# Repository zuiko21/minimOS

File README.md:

*This project is under [the MIT License](https://opensource.org/licenses/MIT), see LICENSE for details.*

# minimOS

*Please note that this doc is OBSOLETE. Read about [updated details in the new 
architecture.md](architecture.md) file.*

#### Minimalistic, portable, scalable Operating System for everything from embedded devices to (quasi) full-featured desktop computers!

## Purpose
Currently in a VERY early development stage, hopefully will become a common reference platform for deployment of computer-related appliances -- think about embedded systems, like the original intent: an Actual Exposure Time Meter for classic photographic cameras. But by virtue of its modularity and scalability would equally serve to a whole breed of home-made, retro-inspided computers.

## Future ports
Initial target is the venerable 65(C)02 and its big brother, the 16-bit enabled 65816 (port known as minimos·16) which will keep compatibility with existing '02 code. But other ports to many CPU architectures are in mind, like the Motorola 68xx / Hitachi 63xx series (minimOS·63, with the interesting 6809/6309 branch as minimOS·69), 680x0 (minimOS·68), 8080/8085/Z80 (minimOS·80), even (God forbid! :-) the commonly used x86 (minimOS·86). I really have little-to-no knowledge about this CPU family, nor about the usual IBM-based PC architecture; hopefully someone will be able to port minimOS without too much of a chore, that would give a very interesting 'breath' to (otherwise useless) older PCs.

## Supported architectures
This section has been moved to the [hardware section](hard/README.md)

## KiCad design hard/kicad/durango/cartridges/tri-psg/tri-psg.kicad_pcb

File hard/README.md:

# Hardware for minimOS

## Supported architectures

With great embarrassment I have to admit never having owned a 65xx computer...
but suport for these classic machines shouldn't be difficult to add -- for
instance, I have declared as 'reserved' the two first zero-page bytes in case
the utterly popular Commodore-64 (using a 6510) is targeted.

Back to my **own-designed** devices, here's the range (past, present and future):

## (Simple) Computers

### 65x02-based

[**MTE** _("Medidor de Tiempos de Exposición", Exposure Time Meter)_](computers/mte.md)

  * Status: finishing design.
  * Form-factor: soldered PCB.
  * Specs: 1 MHz **6503** (28 pin, 4 kiB addressing space), **128-byte RAM**,
3 kiB-EPROM (useable range from a 2732), VIA 6522
  * Peripherals: four (very large) **7-segment LED digits**, light sensor,
a couple of buttons...

[**SDd** _("Sistema de Desarrollo didáctico", Learning Development System)_](computers/sdd.md)

  * Status: [WORKING!](https://twitter.com/zuiko21/status/936654607014653952?s=19)
  * Form-factor: [solderless breadboard.](https://flic.kr/s/aHsjCMszTY)
  * Specs: 1 MHz 65SC02 (only 13 address bits used), **2 kiB RAM, 2-4 kIB (E)EPROM**,
VIA 65C22.
  * Peripherals: Amplified piezo buzzer between PB7-CB2,
currently with a VIA-attached 4-digit **LED-keypad**.

[**CHIHUAHUA**](computers/chihuahua.md)

  * Status: Finished and _sort-of_ working, but with some strange bug around VIA access,
not solved yet. _Likely to be discarded_.
  * Form-factor: [Perfboard with point-to-point soldering.](https://flic.kr/s/aHsjEn5ntM)
  * Peripherals: Piezo buzzer between PB7-CB2
  * Interfaces: **SS-22** and _old **VIAport**_ connectors.

> Soldered, compact version of [SDd](sdd.md).

[**CHIHUAHA PLUS**](computers/chihuahuaplus.md)

  * Status: [under construction (recently redesigned).](https://flic.kr/s/aHsjEGuCH3)
  * Form-factor: Perfboard with point-to-point soldering.
  * Specs: **1 MHz (socketed XTAL)** 65C02, **16 kiB RAM, 32 kiB EPROM**, VIA 65C22.
_Can be configured for **32 kiB RAM + 16 kiB EPROM** if desired_.
  * Peripherals: _Amplified_ piezo buzzer between PB7-CB2
  * Interfaces: **SS-22** and _old **VIAport**_ connectors.

[**miniKIM**](computers/minikim.md)

  * Status: finishing specs.
  * Form-factor: Perfboard with point-to-point soldering.
  * Specs: 1 MHz 6502, **32 kiB RAM (16 KiB available), 2x16 kiB EPROM**, 2xVIA 6522,
ready for _cheap video_ output. _May use 32K RAM and 16K EPROM_ instead.
  * Peripherals: original KIM keypad, **6x seven-segment displays** (muxed LTC4622).
  * Interfaces: original Application & Expansion slots, _upstream tap_ for **cheap video**.

[**DURANGO**](computers/durango.md)

  * Status: **working**.
  * Form-factor: several solderless breadboards.
  * Specs: 1 MHz 6502, **32 kiB RAM, 16 kiB EPROM**, includes **picoVDU**
TV video output (128x128 _bitmap_).
  * Peripherals: simple bit buzzer, **2x seven-segment displays** (muxed LTC4622).
  * Interfaces: 8-bit input (`IO9`), 8-bit output for _picoVDU_ (`IO8`)

> Originally intended as a **6502 CPU tester** with _no I/O_ whatsoever, it evolved
into a fully featured development platform with sort-of integrated **video output**.
_May become a definitive, improved version in perfboard_

[**miniPET**](computers/minipet.md)

  * Status: **essentially finished** design.
  * Form-factor: Perfboard with point-to-point soldering.
  * Specs: **1.57 MHz** 65(C)02, **32 kiB SRAM** (plus 2 kiB _VRAM_), up to
**32 kiB EPROM**, VIA 65(C)22, PIA 6521/6821, CRTC HD6845, with _optional second PIA_
for **IEEE-488** interface.
  * Interfaces: **same as the original PET**; cassette and IEEE-488 on separate
_optional_ board.

> _This is a recreation of the **Commodore PET/CBM 8032**, 
switchable between **40 and 80 columns**_, with updated components
(e.g. SRAM) and **VGA-compatible** output (thus about **57% faster**).

[**Tampico**](computers/tampico.md)

  * Status: finishing specs.
  * Form-factor: Perfboard with point-to-point soldering.
  * Specs: **1.536 MHz** 65C02, **32 kiB SRAM**, **32 kiB EPROM**, VIA 65C22, CRTC HD6845/6445.
  * Peripherals: Piezo buzzer, **VGA-compatible** video output
(**320x200/288x224 bitmap** with options of _**400/448 lines**_ and _**2 bpp colour**_)
  * Interfaces: SS-22, new VIA connector.

> A _black & white_ version of **Acapulco**, albeit with a 'high' resolution option.
_Might include a 6551-based TTL serial_.
> Optional **2 bpp colour mode** by halving horizontal resolution.

[**Acapulco**](computers/acapulco.md)

  * Status: almost finished design.
  * Form-factor: Perfboard with point-to-point soldering.
  * Specs: **1.536 MHz** 65C02, **32 kiB SRAM** (plus 1 kiB in parallel as
_attribute area_, **32 kiB EPROM**, VIA 65C22, CRTC HD6445.
_Intended to be a **colour & graphics** capable SBC._
  * Peripherals: Piezo buzzer, **VGA-compatible** video output
(**320x200/228x224 @ 16 colours** in gBRG mode, only 2 of them on any 8x8-pixel block)
  * Interfaces: SS-22, new VIA connector.

> _May use an **alternate attribute area**, as CRAM is really 2 kiB_.

### 65816-based

[**Jalapa** (formerly _SDm_)](computers/jalapa2.md)

  * Status: almost finished design, heavily _revamped_ as of Oct-2018.
  * Form-factor: Perfboard with point-to-point soldering.
  * Specs: 1.8432 / 2.304 MHz **65816**, **128-512 kiB RAM**,
up to **32 kiB _Kernel_ EPROM** plus **up to 512 kiB _library_ EPROM**,
VIA 65C22 (x2?), ACIA 65SC51, ROM-in-RAM, RTC 146818 (?).
  * Peripherals: Amplified piezo buzzer between PB7-CB2.
  * Interfaces: SS-22, new _VIAport**2**_ (_SBC-2_ style but with "mirrored" power pins),
TTL-level RS-232, **_VME-like_ slot** (65816 direct expansion).

> **Development system**, much like the former _SDx_ project.

[**Tijuana**](computers/tijuana.md)

  * Status: finishing design, _revamped as 20200413_
  * Form-factor: Single layer PCB?
  * Specs: **3.072 MHz 65816**, 128 kiB SRAM (expandable to **512 kB**),
(optional?) 32 kiB **ColourRAM**, 32 kiB EPROM, VIA 65C22, **CRTC HD6845**, ACIA 6551A.
  * Peripherals: Piezo buzzer, **VGA-compatible** video output (**640x400/576x448**
bitmap or up to **4bpp** on 8x1 _attribute area_, gBRG or greyscale?).
  * Interfaces: TTL-level async., SS-22, VIAport2.

> _Intended to be a **graphics** (and perhaps _colour_) capable **VT-52** based terminal_,
a bit like an '816-based **Tampico** computer. Might use a 16C550 instead of the 6551.

[**Tantoyuca**](computers/tantoyuca.md)

  * Status: creating specs
  * Form-factor: Single layer PCB?
  * Specs: **3.072 MHz 65816**, 128 kiB SRAM (expandable to **512 kB**),
32 kiB EPROM, VIA 65C22, **CRTC HD6845**, ACIA 6551A.
  * Peripherals: Piezo buzzer, **VGA-compatible** video output
  * Display resolution: **640x400/576x448**
bitmap, **320x400/288x448 2bpp** or **160x400/144x448 _gBRG_ 4bpp**.
Might reduce vertical resolution to 200/224 lines for reduced 16 kiB
_vampire video_ memory.
  * Interfaces: TTL-level async., SS-22, VIAport2.

> _Might become integrated with the Tijuana project_, a bit like an
'816-based **Tampico** computer. Might use a 16C550 instead of the 6551.
Might switch between high and low resolution (400/448 vs. 200/224 lines)
thru the `E` line, _remapping VRAM_ from $10000-$17FFF to just 16 kiB at
$4000-7FFF, more suitable for 6502 emulation mode.

##  Workstations (65816-based)

[**Veracruz**](computers/veracruz.md)

  * Status: in design stage.
  * Form-factor: thru-hole PCB?
  * Specs: **6.144 MHz 65816**, 512 kiB RAM, 32 kiB _Kernel_ EPROM, 512 kiB _lib_ EPROM,
2x VIA 65C22, UART 16C550, RTC MC146818 (?), ROM-in-RAM. 
  * Peripherals: Piezo buzzer, Hitachi LCD thru VIA (?).
  * Interfaces: new VIA and SS-22 connectors, TTL-level async, **65SIB** (?), **PS/2**,
_VME-like_ slot (65816 direct expansion).

> _Likely to include a **4bpp, 640x400/576x448 px** card (becoming the **SIXtation Lite**)_

[**Jalisco**](computers/jalisco.md) _(CPU card for **SIXtation**)_

  * Status: in design stage.
  * Form-factor: 4-layer PCB, SMD components.
  * Specs: **7.16-9 MHz 65816**, **68881/882 FPU**, **1 MiB RAM, expandable**
(2 x Garth's modules), 32 kiB Kernel + **4 MiB _lib_ EPROM**, 2x or 3x VIA 65C22,
UART 16C552, RTC MC146818, _ROM-in-RAM_.
  * Peripherals: most likely those of _Veracruz_, plus CF & SD-card.
  * Interfaces: most likely those of _Veracruz_, including **65SIB**, _VME-like slot_...

> The 7.16 MHz version is the CPU card for _SIXtation-P_ (**640x864 px**),
while the standard model uses a **9 MHz** clock (**1360x768 px**).

[**Tabasco**](computers/tabasco.md) _(CPU card for **SIXtation TURBO**)_

  * Status: in design stage.
  * Form-factor: 4-layer PCB, SMD components.
  * Specs: **13.5 MHz 65816**, **68881/882 FPU**, **1 MiB RAM, expandable**
(2 x Garth's modules), 32 kiB Kernel + **4 MiB _lib_ EPROM**, 2x or 3x VIA 65C22,
UART 16C552, RTC MC146818, _ROM-in-RAM_.
  * Peripherals: most likely those of _Jalisco_, plus CF & SD-card.
  * Interfaces: most likely those of _Jalisco_.

[**SIXtation**](computers/sixtation.md) _essentially a **Jalisco/Tabasco** CPU card with an 8-plane VDU_

  * Status: in design stage.
  * Form-factor: 4-layer PCB, SMD components.
  * Specs: **9 MHz 65816** (base model), **24.576 MHz 68881 FPU** (or faster), up to
**8-9 MiB RAM** using the _Jalisco_ (or _Tabasco_) CPU card.
  * Video output: VGA, 6445-based, _planar_ up to 8x128 kiB VRAM and **8 bpp**, typically
**1360x768 px**. 24-bit CLUT.
  * Other interfaces: those of _Jalisco/Tabasco_.

> Range include the P (portrait) version (**7.16 MHz, 640x864 px**) and _TURBO_ model
(**13.5 MHz, 1152x896 px**). Also the FPU-less, Veracruz-based _SIXtation Lite_
(**6.144 MHz, 576x448 px, 4 bpp**).

## Aborted projects (6502-based)

[**SDx _("Sistema de Desarrollo eXpandible", Expansible Develpment 
System)_**](https://flic.kr/s/aHsjDAwJBR)

  * Status: aborted during construction :-(
  * Form-factor: Perfboard with point-to-point soldering.
  * Specs: 1.25 / 2 MHz 65C02/102, 8-16 kIB RAM, 32 kiB EPROM, VIA 65C22,
ACIA 65SC51, RTC 146818.
  * Peripherals: Amplified piezo buzzer between PB7-CB2, several diagnostic LEDs.
  * Interfaces: Hitachi LCD, TTL-level RS-232, SS-22 and old _VIAport_ connectors.

**Baja**

  * Status: never started :-(

> Intended to be a **fully _bankswitching_ 65C02 SBC**, but pluggable into a backplane, too.

## Non-65xx architectures

### Motorola 6800 & 6809-based

[**KERAton**](https://flic.kr/p/dUEH5s)

  * Specs: 921.6 kHz **MC6800, 128-byte RAM**, up to 32 kiB EPROM,
PIA **CM602** (MC6820 clone), ACIA 2651.

> Made from **ceramic**-cased ICs only.

[**miniAlice**](computers/minialice.md)

  * Specs: 895 kHz **MC6803** _MCU_, **8 KiB** SRAM, **MC6847** video (with _RGB_ output).

> Recreation of Tandy's **TRS-80 _MC-10_**), perhaps switchable to mimic its French clone
**Matra & Hachette _Alice_** (AZERTY keyboard).

[**miniCoCo**](computers/minicoco.md)

  * Specs: 895 kHz **MC6809**, 32-64 KiB **S**RAM, 2x PIA 6821,
**MC6847 video** (with _RGB_ output).

> Recreation of Tandy's **TRS-80 _Color Computer_** (version 1), switchable to
mimic the highly compatible **Dragon 32/64**.

## Peripherals (TBD)

**LED-Keypad**

  * Status: [WORKING!](https://flic.kr/p/dL6Nec)
  * Form-factor: solderless breadboard.
  * Specs: four 7-segment LED displays, 16-key keypad.
  * Interface: old-style _VIAport_ connector.

> Intended as a basic I/O device, current driver allows hex input via a _shift_ key.

**ASCII Keyboard**

  * Status: [in design stage.](https://flic.kr/p/e7C1mS)
  * Form-factor: solderless breadboard.
  * Specs: **64 keys**, two sets of three modifier keys. _May include a 20x4 LCD_.
  * Interface: old-style _VIAport_ connector, thinking about using the new **VIAport2**.

> Conveniently laid out keyboard, the use of an **optional LCD** will make a
_self-contained simple terminal_.

**[PASK (_Port-'A' Simple Keyboard_)](peripheral/pask.md)**

  * Status: in design stage.
  * Specs: **40 keys** including the three usual _modifiers_: `Shift`, `Ctrl` and `Alt`.
  * Interface: single **VIAport2**, supposedly compatible with _Centronics_
printer interface.

> A self-contained keyboard, supported by a **minimal driver**.  Allows input of the
**full 8-bit** ASCII set.

**[Roñavid](peripheral/roñavid.md)**

  * Status: (almost) finished design.
  * Specs: **VGA-compatible** output, typically **640x400/576x448 _bitmap_** or
**320x200/288x224 @ 4bpp** _chunky_).
  * Interface: _VME-like bus_.
  
> _Somewhat cumbersome_ **video card**. No CRTC, just _suitably programmed EPROMs_
generating all needed addresses and signals.

**[mu-VDU](peripheral/mu-vdu.md)**

  * Status: (almost) finished design.
  * Specs: **VGA-compatible** output of **320x200/288x224px bitmap**.
  * Interface: **6502-CPU _socket_**

> Simple, universal **graphic display**. _An extended **planar** version might provide
**8 colours**_.

**[pico-VDU](peripheral/pico-vdu.md)**

  * Status: **working**.
  * Specs: PAL TV output of **128x128/256x256px bitmap**.
  * Interface: **6502-CPU _socket_**, also available as _IOchannel_ and **VIAbus**

> Simple, universal **graphic display**, also integrated in _DURANGO_.
---
_...and many more to come!_

_last modified: 20210312-1428_

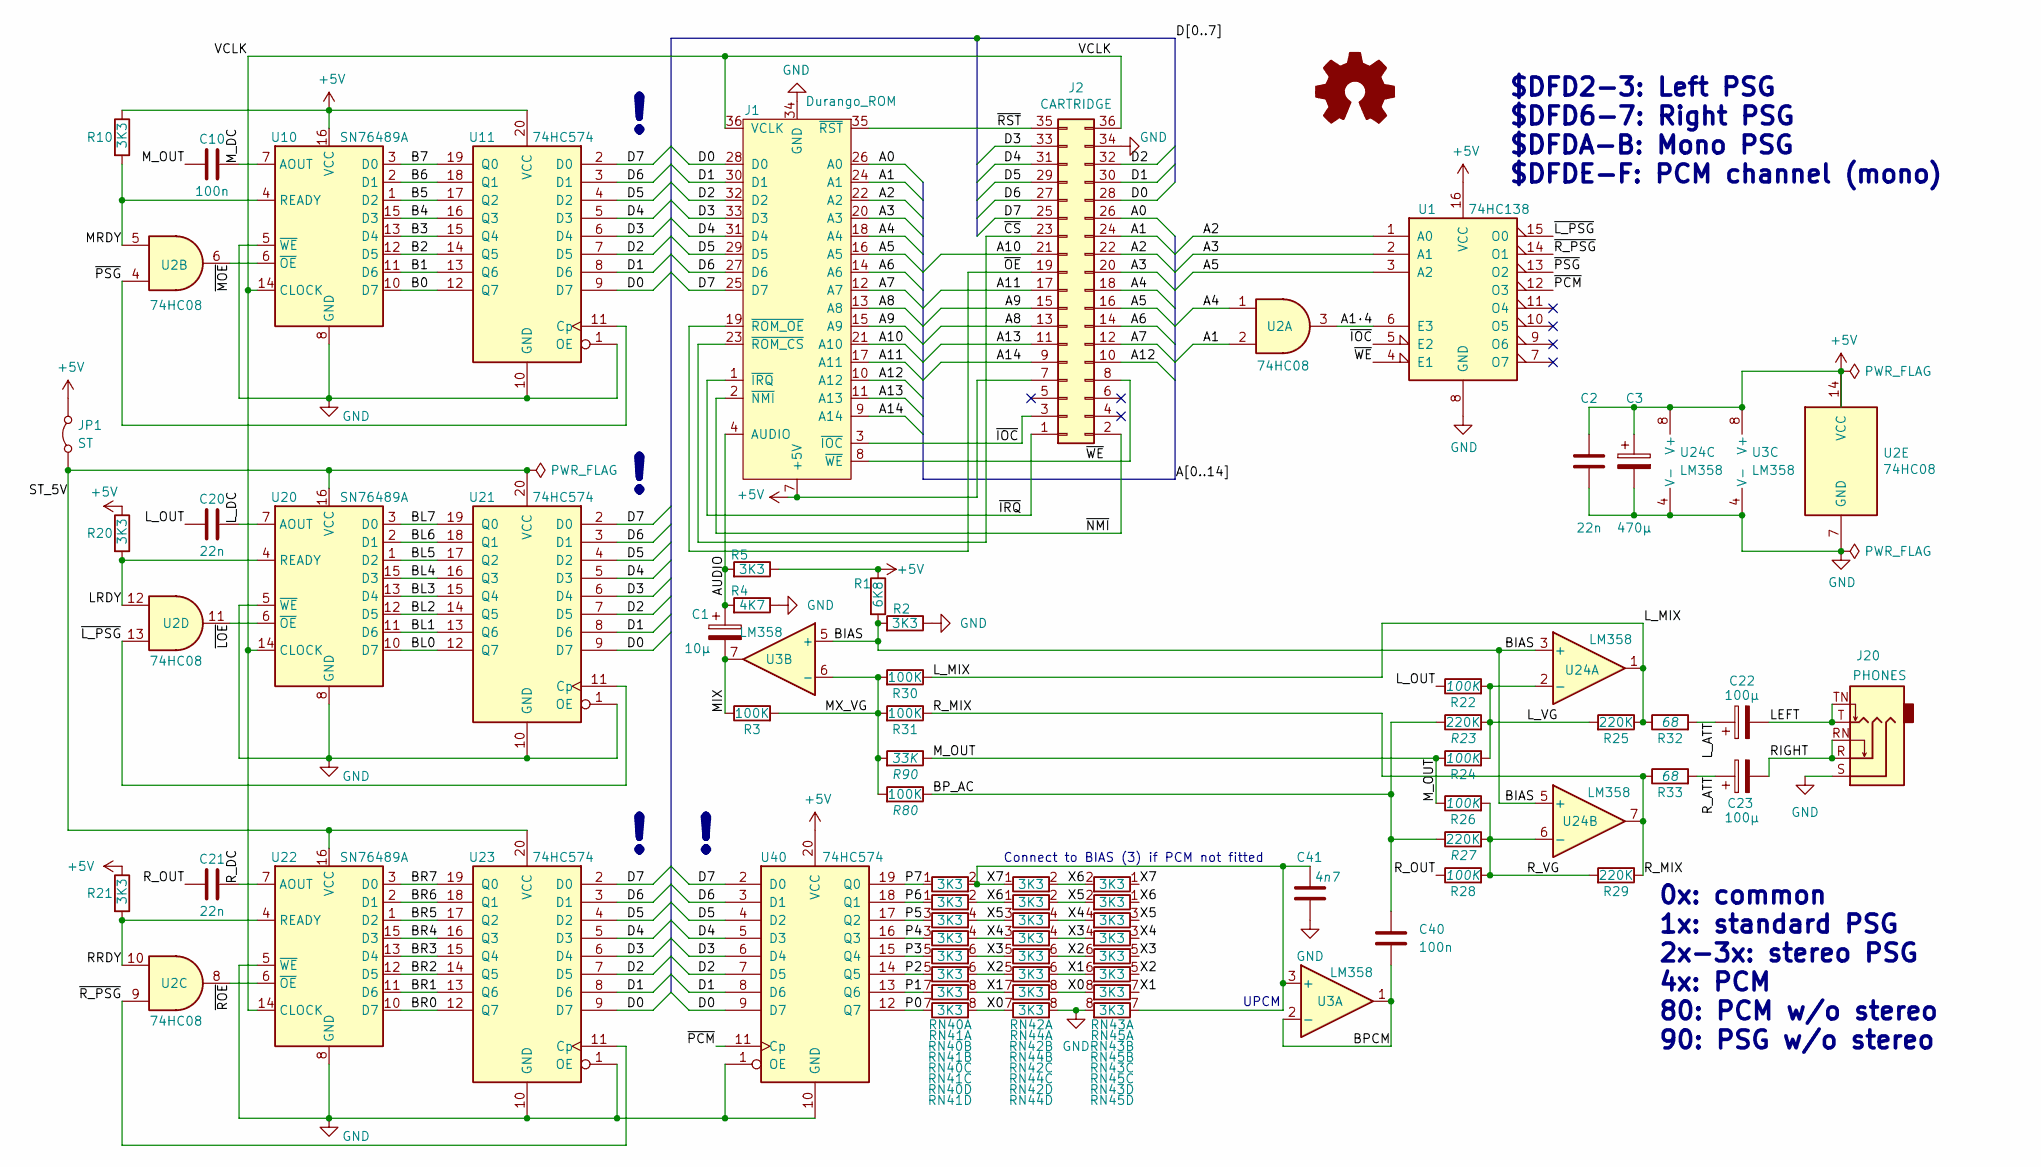
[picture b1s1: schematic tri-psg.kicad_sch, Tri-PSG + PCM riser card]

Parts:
C1: 10µ; CP_Radial_D4.0mm_P1.50mm
C2, C20, C21: 22n; C_Disc_D6.0mm_W2.5mm_P5.00mm
C3: 470µ; CP_Radial_D6.3mm_P2.50mm
C10, C40: 100n; C_Rect_L7.2mm_W2.5mm_P5.00mm_FKS2_FKP2_MKS2_MKP2
C22, C23: 100µ; CP_Radial_D4.0mm_P1.50mm
C41: 4n7; C_Disc_D3.8mm_W2.6mm_P2.50mm
J1: Durango_ROM
J2: CARTRIDGE; PinSocket_2x18_EDGE
J20: PHONES; Jack_3.5mm_CUI_SJ1-3525N_Horizontal
JP1: ST; PinHeader_1x02_P2.54mm_Vertical
LOGO1: Logo_Open_Hardware_Small; j300
R1: 6K8; R_Axial_DIN0207_L6.3mm_D2.5mm_P2.54mm_Vertical
R2, R5, R10, R20, R21: 3K3; R_Axial_DIN0207_L6.3mm_D2.5mm_P2.54mm_Vertical
R3, R22, R24, R26, R28, R30, R31, R80: 100K; R_Axial_DIN0207_L6.3mm_D2.5mm_P2.54mm_Vertical
R4: 4K7; R_Axial_DIN0207_L6.3mm_D2.5mm_P2.54mm_Vertical
R23, R25, R27, R29: 220K; R_Axial_DIN0207_L6.3mm_D2.5mm_P2.54mm_Vertical
R32, R33: 68; R_Axial_DIN0207_L6.3mm_D2.5mm_P2.54mm_Vertical
R90: 33K; R_Axial_DIN0207_L6.3mm_D2.5mm_P2.54mm_Vertical
RN40, RN41, RN42, RN43, RN44, RN45: 3K3; R_Array_SIP8
U1: 74HC138; DIP-16_W7.62mm_Socket
U2: 74HC08; DIP-14_W7.62mm_Socket
U3, U24: LM358; DIP-8_W7.62mm_Socket
U10, U20, U22: SN76489A; DIP-16_W7.62mm_Socket
U11, U21, U23, U40: 74HC574; DIP-20_W7.62mm_Socket

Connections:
+5V: C2.2, C3.1, J1.7 (+5V), J2.7, JP1.2 (B), R1.1, R5.1, R10.1, R20.1, R21.1, U1.16 (VCC), U2.14 (VCC), U3.8 (V+), U10.16 (VCC), U11.20 (VCC), U24.8 (V+), U40.20 (VCC)
/A0: J1.26 (A0), J2.26
/A1: J1.24 (A1), J2.24, U2.2
/A1·4: U1.6 (E3), U2.3
/A2: J1.22 (A2), J2.22, U1.1 (A0)
/A3: J1.20 (A3), J2.20, U1.2 (A1)
/A4: J1.18 (A4), J2.18, U2.1
/A5: J1.16 (A5), J2.16, U1.3 (A2)
/A6: J1.14 (A6), J2.14
/A7: J1.12 (A7), J2.12
/A8: J1.13 (A8), J2.13
/A9: J1.15 (A9), J2.15
/A10: J1.21 (A10), J2.21
/A11: J1.17 (A11), J2.17
/A12: J1.10 (A12), J2.10
/A13: J1.11 (A13), J2.11
/A14: J1.9 (A14), J2.9
/AUDIO: C1.1, J1.4 (AUDIO), R4.2, R5.2
/B0: U10.10 (D7), U11.12 (Q7)
/B1: U10.11 (D6), U11.13 (Q6)
/B2: U10.12 (D5), U11.14 (Q5)
/B3: U10.13 (D4), U11.15 (Q4)
/B4: U10.15 (D3), U11.16 (Q3)
/B5: U10.1 (D2), U11.17 (Q2)
/B6: U10.2 (D1), U11.18 (Q1)
/B7: U10.3 (D0), U11.19 (Q0)
/BIAS: R1.2, R2.2, U3.5 (+), U24.3 (+), U24.5 (+)
/BL0: U20.10 (D7), U21.12 (Q7)
/BL1: U20.11 (D6), U21.13 (Q6)
/BL2: U20.12 (D5), U21.14 (Q5)
/BL3: U20.13 (D4), U21.15 (Q4)
/BL4: U20.15 (D3), U21.16 (Q3)
/BL5: U20.1 (D2), U21.17 (Q2)
/BL6: U20.2 (D1), U21.18 (Q1)
/BL7: U20.3 (D0), U21.19 (Q0)
/BPCM: C40.2, U3.1, U3.2 (-)
/BP_AC: C40.1, R23.1, R27.1, R80.1
/BR0: U22.10 (D7), U23.12 (Q7)
/BR1: U22.11 (D6), U23.13 (Q6)
/BR2: U22.12 (D5), U23.14 (Q5)
/BR3: U22.13 (D4), U23.15 (Q4)
/BR4: U22.15 (D3), U23.16 (Q3)
/BR5: U22.1 (D2), U23.17 (Q2)
/BR6: U22.2 (D1), U23.18 (Q1)
/BR7: U22.3 (D0), U23.19 (Q0)
/D0: J1.28 (D0), J2.28, U11.9 (D7), U21.9 (D7), U23.9 (D7), U40.9 (D7)
/D1: J1.30 (D1), J2.30, U11.8 (D6), U21.8 (D6), U23.8 (D6), U40.8 (D6)
/D2: J1.32 (D2), J2.32, U11.7 (D5), U21.7 (D5), U23.7 (D5), U40.7 (D5)
/D3: J1.33 (D3), J2.33, U11.6 (D4), U21.6 (D4), U23.6 (D4), U40.6 (D4)
/D4: J1.31 (D4), J2.31, U11.5 (D3), U21.5 (D3), U23.5 (D3), U40.5 (D3)
/D5: J1.29 (D5), J2.29, U11.4 (D2), U21.4 (D2), U23.4 (D2), U40.4 (D2)
/D6: J1.27 (D6), J2.27, U11.3 (D1), U21.3 (D1), U23.3 (D1), U40.3 (D1)
/D7: J1.25 (D7), J2.25, U11.2 (D0), U21.2 (D0), U23.2 (D0), U40.2 (D0)
/LEFT: C22.2, J20.T, J20.TN
/LRDY: R20.2, U2.12, U20.4 (READY)
/L_ATT: C22.1, R32.2
/L_DC: C20.2, U20.7 (AOUT)
/L_MIX: R25.1, R30.1, R32.1, U24.1
/L_OUT: C20.1, R22.1
/L_VG: R22.2, R23.2, R24.2, R25.2, U24.2 (-)
/MIX: C1.2, R3.1, U3.7
/MRDY: R10.2, U2.5, U10.4 (READY)
/MX_VG: R3.2, R30.2, R31.2, R80.2, R90.2, U3.6 (-)
/M_DC: C10.2, U10.7 (AOUT)
/M_OUT: C10.1, R24.1, R26.1, R90.1
/P0: RN41.7 (R4.1), U40.12 (Q7)
/P1: RN40.7 (R4.1), U40.13 (Q6)
/P2: RN41.5 (R3.1), U40.14 (Q5)
/P3: RN40.5 (R3.1), U40.15 (Q4)
/P4: RN41.3 (R2.1), U40.16 (Q3)
/P5: RN40.3 (R2.1), U40.17 (Q2)
/P6: RN41.1 (R1.1), U40.18 (Q1)
/P7: RN40.1 (R1.1), U40.19 (Q0)
/RIGHT: C23.2, J20.R, J20.RN
/RRDY: R21.2, U2.10, U22.4 (READY)
/R_ATT: C23.1, R33.2
/R_DC: C21.2, U22.7 (AOUT)
/R_MIX: R29.1, R31.1, R33.1, U24.7
/R_OUT: C21.1, R28.1
/R_VG: R26.2, R27.2, R28.2, R29.2, U24.6 (-)
/ST_5V: JP1.1 (A), U20.16 (VCC), U21.20 (VCC), U22.16 (VCC), U23.20 (VCC)
/VCLK: J1.36 (VCLK), J2.36, U10.14 (CLOCK), U20.14 (CLOCK), U22.14 (CLOCK)
/X0: RN41.8 (R4.2), RN42.8 (R4.2), RN43.8 (R4.2), RN44.7 (R4.1)
/X1: RN40.8 (R4.2), RN42.7 (R4.1), RN43.7 (R4.1), RN44.6 (R3.2), RN45.6 (R3.2)
/X2: RN41.6 (R3.2), RN42.6 (R3.2), RN43.6 (R3.2), RN44.5 (R3.1), RN45.5 (R3.1)
/X3: RN40.6 (R3.2), RN42.5 (R3.1), RN43.5 (R3.1), RN44.4 (R2.2), RN45.4 (R2.2)
/X4: RN41.4 (R2.2), RN42.4 (R2.2), RN43.4 (R2.2), RN44.3 (R2.1), RN45.3 (R2.1)
/X5: RN40.4 (R2.2), RN42.3 (R2.1), RN43.3 (R2.1), RN44.2 (R1.2), RN45.2 (R1.2)
/X6: RN41.2 (R1.2), RN42.2 (R1.2), RN43.2 (R1.2), RN44.1 (R1.1), RN45.1 (R1.1)
/X7: C41.1, RN40.2 (R1.2), RN42.1 (R1.1), RN43.1 (R1.1), RN45.7 (R4.1), U3.3 (+)
/~CS: J1.23 (~ROM_CS), J2.23
/~IOC: J1.3 (~IOC), J2.3, U1.5 (E2)
/~IRQ: J1.1 (~IRQ), J2.1
/~LOE: U2.11, U20.6 (~OE)
/~L_PSG: U1.15 (O0), U2.13, U21.11 (Cp)
/~MOE: U2.6, U10.6 (~OE)
/~NMI: J1.2 (~NMI), J2.2
/~OE: J1.19 (~ROM_OE), J2.19
/~PCM: U1.12 (O3), U40.11 (Cp)
/~PSG: U1.13 (O2), U2.4, U11.11 (Cp)
/~ROE: U2.8, U22.6 (~OE)
/~RST: J1.35 (~RST), J2.35
/~R_PSG: U1.14 (O1), U2.9, U23.11 (Cp)
/~WE: J1.8 (~WE), J2.8, U1.4 (E1)
GND: C2.1, C3.2, C41.2, J1.34 (GND), J2.34, J20.S, R2.1, R4.1, RN44.8 (R4.2), RN45.8 (R4.2), U1.8 (GND), U2.7 (GND), U3.4 (V-), U10.5 (~WE), U10.8 (GND), U11.1 (OE), U11.10 (GND), U20.5 (~WE), U20.8 (GND), U21.1 (OE), U21.10 (GND), U22.5 (~WE), U22.8 (GND), U23.1 (OE), U23.10 (GND), U24.4 (V-), U40.1 (OE), U40.10 (GND)

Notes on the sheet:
0x: common 1x: standard PSG 2x-3x: stereo PSG 4x: PCM 80: PCM w/o stereo 90: PSG w/o stereo
Connect to BIAS (3) if PCM not fitted
UPCM
$DFD2-3: Left PSG $DFD6-7: Right PSG $DFDA-B: Mono PSG $DFDE-F: PCM channel (mono)

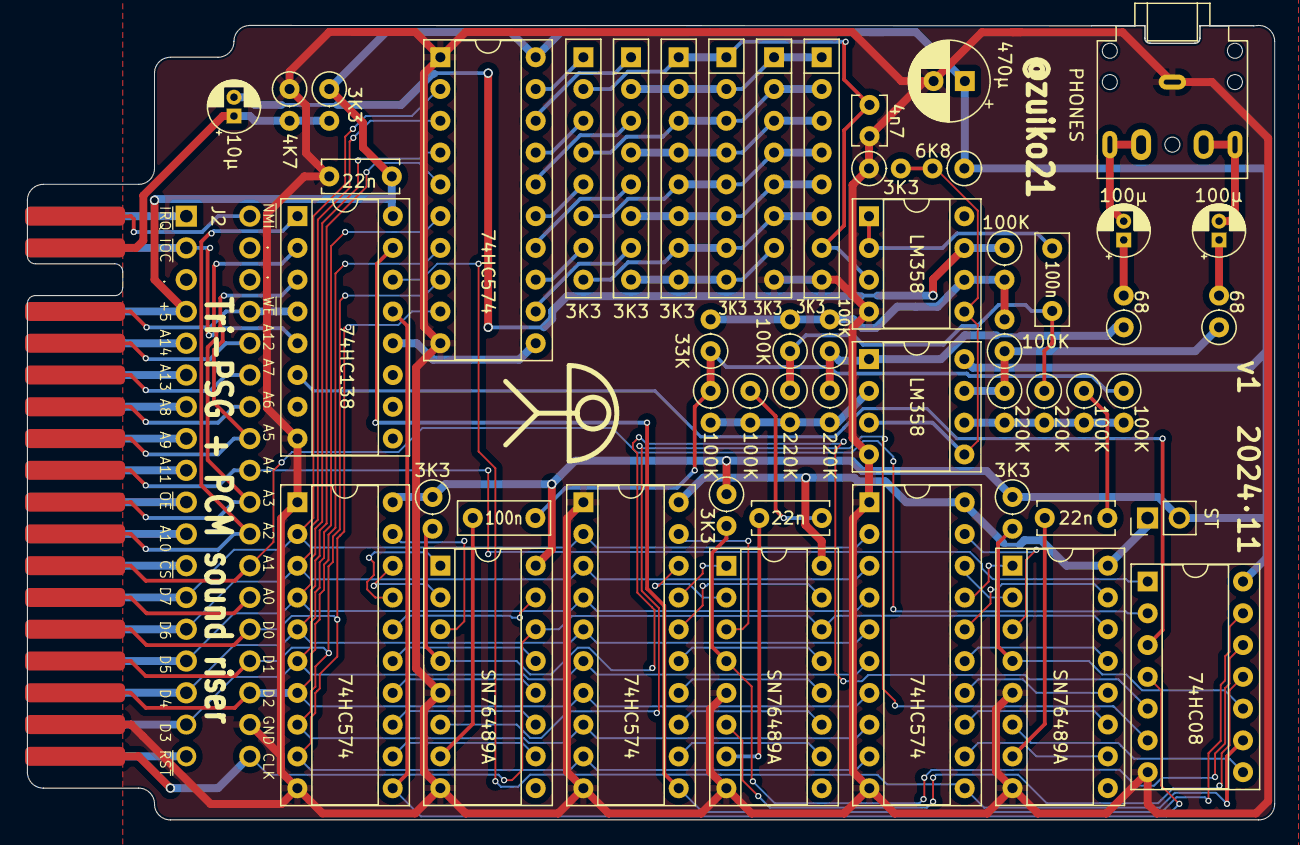
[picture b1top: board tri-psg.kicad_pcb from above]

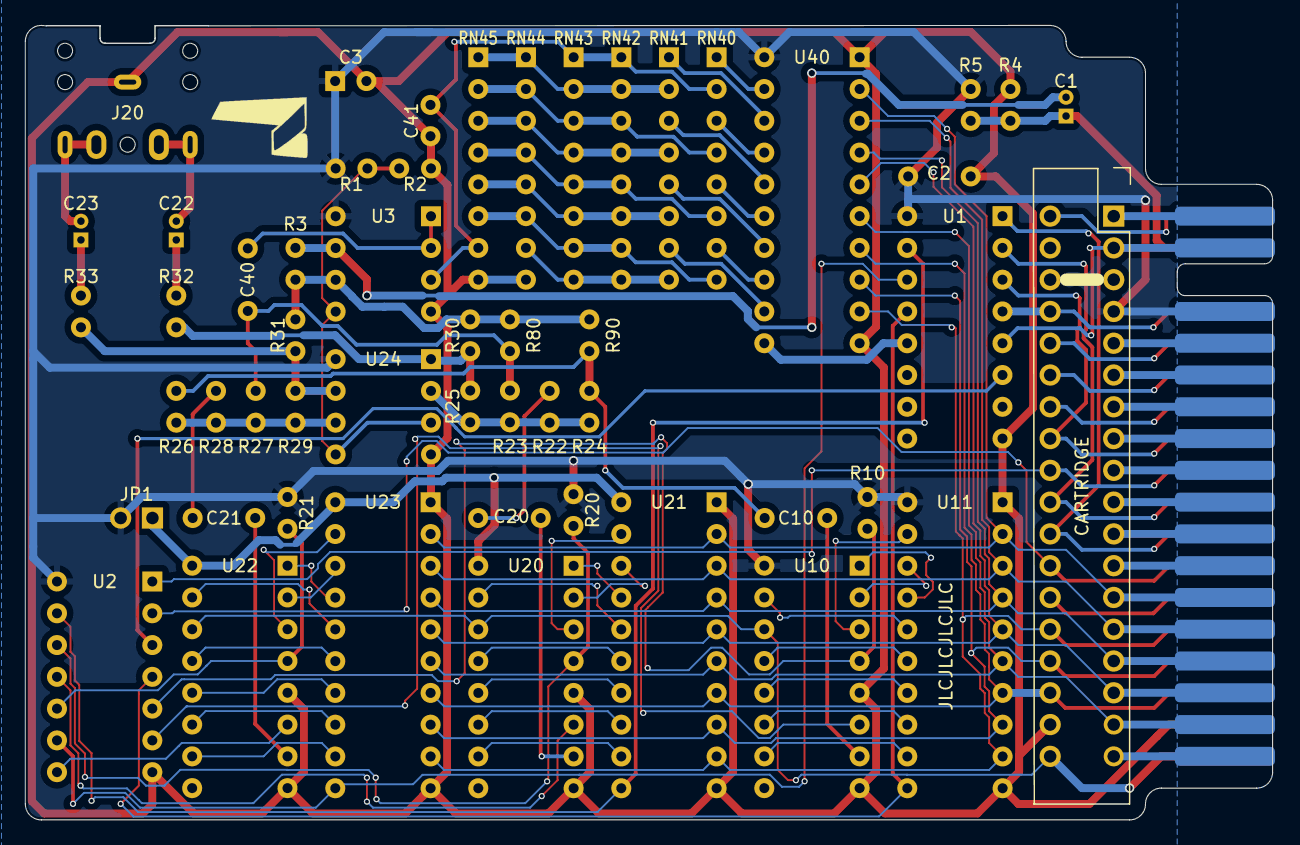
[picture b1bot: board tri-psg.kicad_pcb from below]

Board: 2 copper layers, 99.7 x 63.5 mm, 54 parts (3 on the bottom side), 105 nets.

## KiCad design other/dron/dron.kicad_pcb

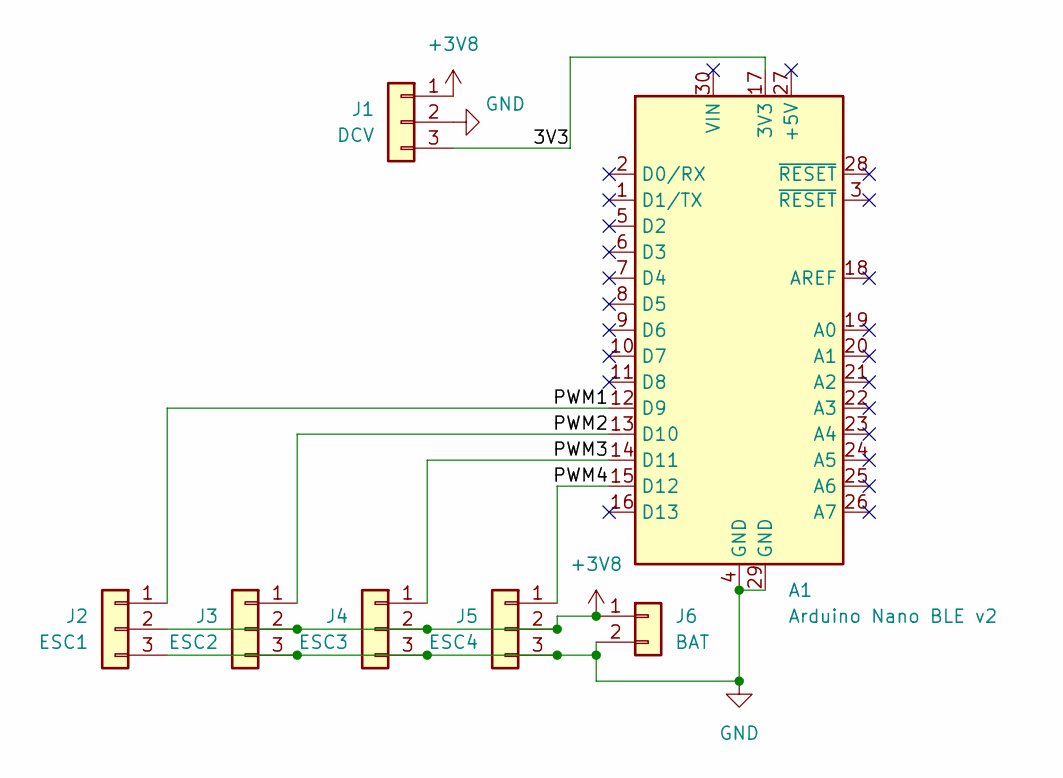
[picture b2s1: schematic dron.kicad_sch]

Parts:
A1: Arduino Nano BLE v2; Arduino_Nano
J1: DCV; PinHeader_1x03_P2.54mm_Vertical
J2: ESC1; PinHeader_1x03_P2.54mm_Vertical
J3: ESC2; PinHeader_1x03_P2.54mm_Vertical
J4: ESC3; PinHeader_1x03_P2.54mm_Vertical
J5: ESC4; PinHeader_1x03_P2.54mm_Vertical
J6: BAT; JST_PH_B2B-PH-K_1x02_P2.00mm_Vertical

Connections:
+3V8: J1.1, J2.2, J3.2, J4.2, J5.2, J6.1
/3V3: A1.17 (3V3), J1.3
/PWM1: A1.12 (D9), J2.1
/PWM2: A1.13 (D10), J3.1
/PWM3: A1.14 (D11), J4.1
/PWM4: A1.15 (D12), J5.1
GND: A1.4 (GND), A1.29 (GND), J1.2, J2.3, J3.3, J4.3, J5.3, J6.2

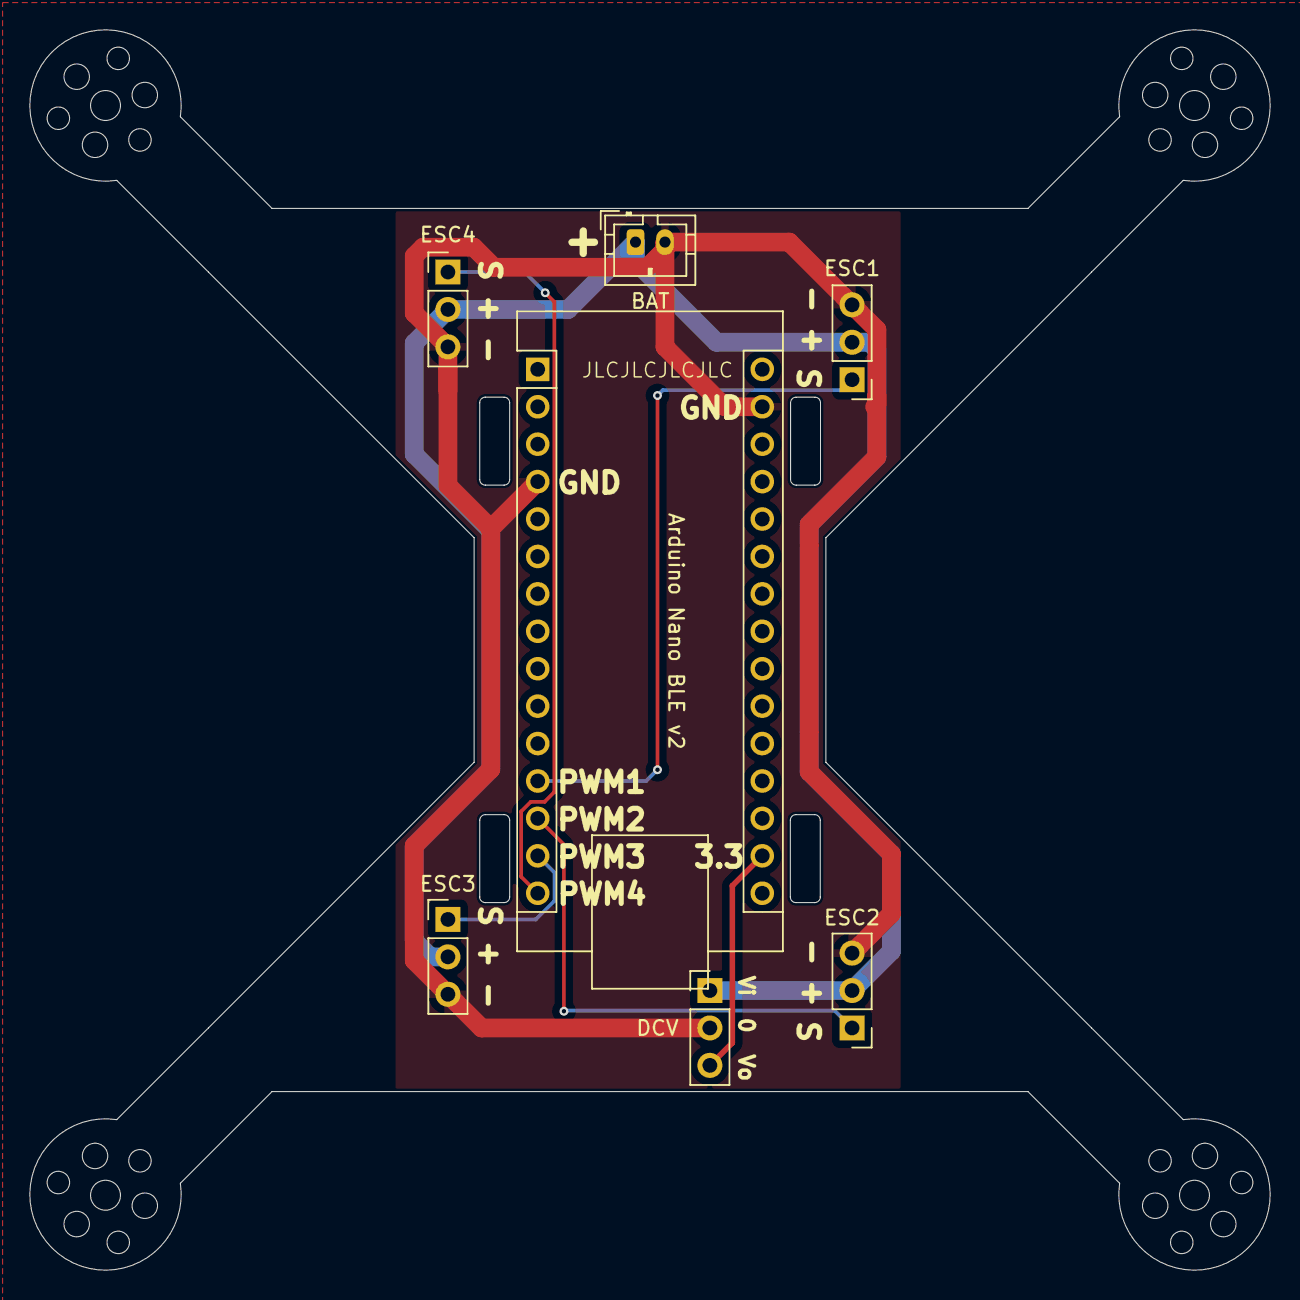
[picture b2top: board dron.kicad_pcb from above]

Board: 2 copper layers, 84.2 x 84.2 mm, 7 parts (0 on the bottom side), 7 nets.

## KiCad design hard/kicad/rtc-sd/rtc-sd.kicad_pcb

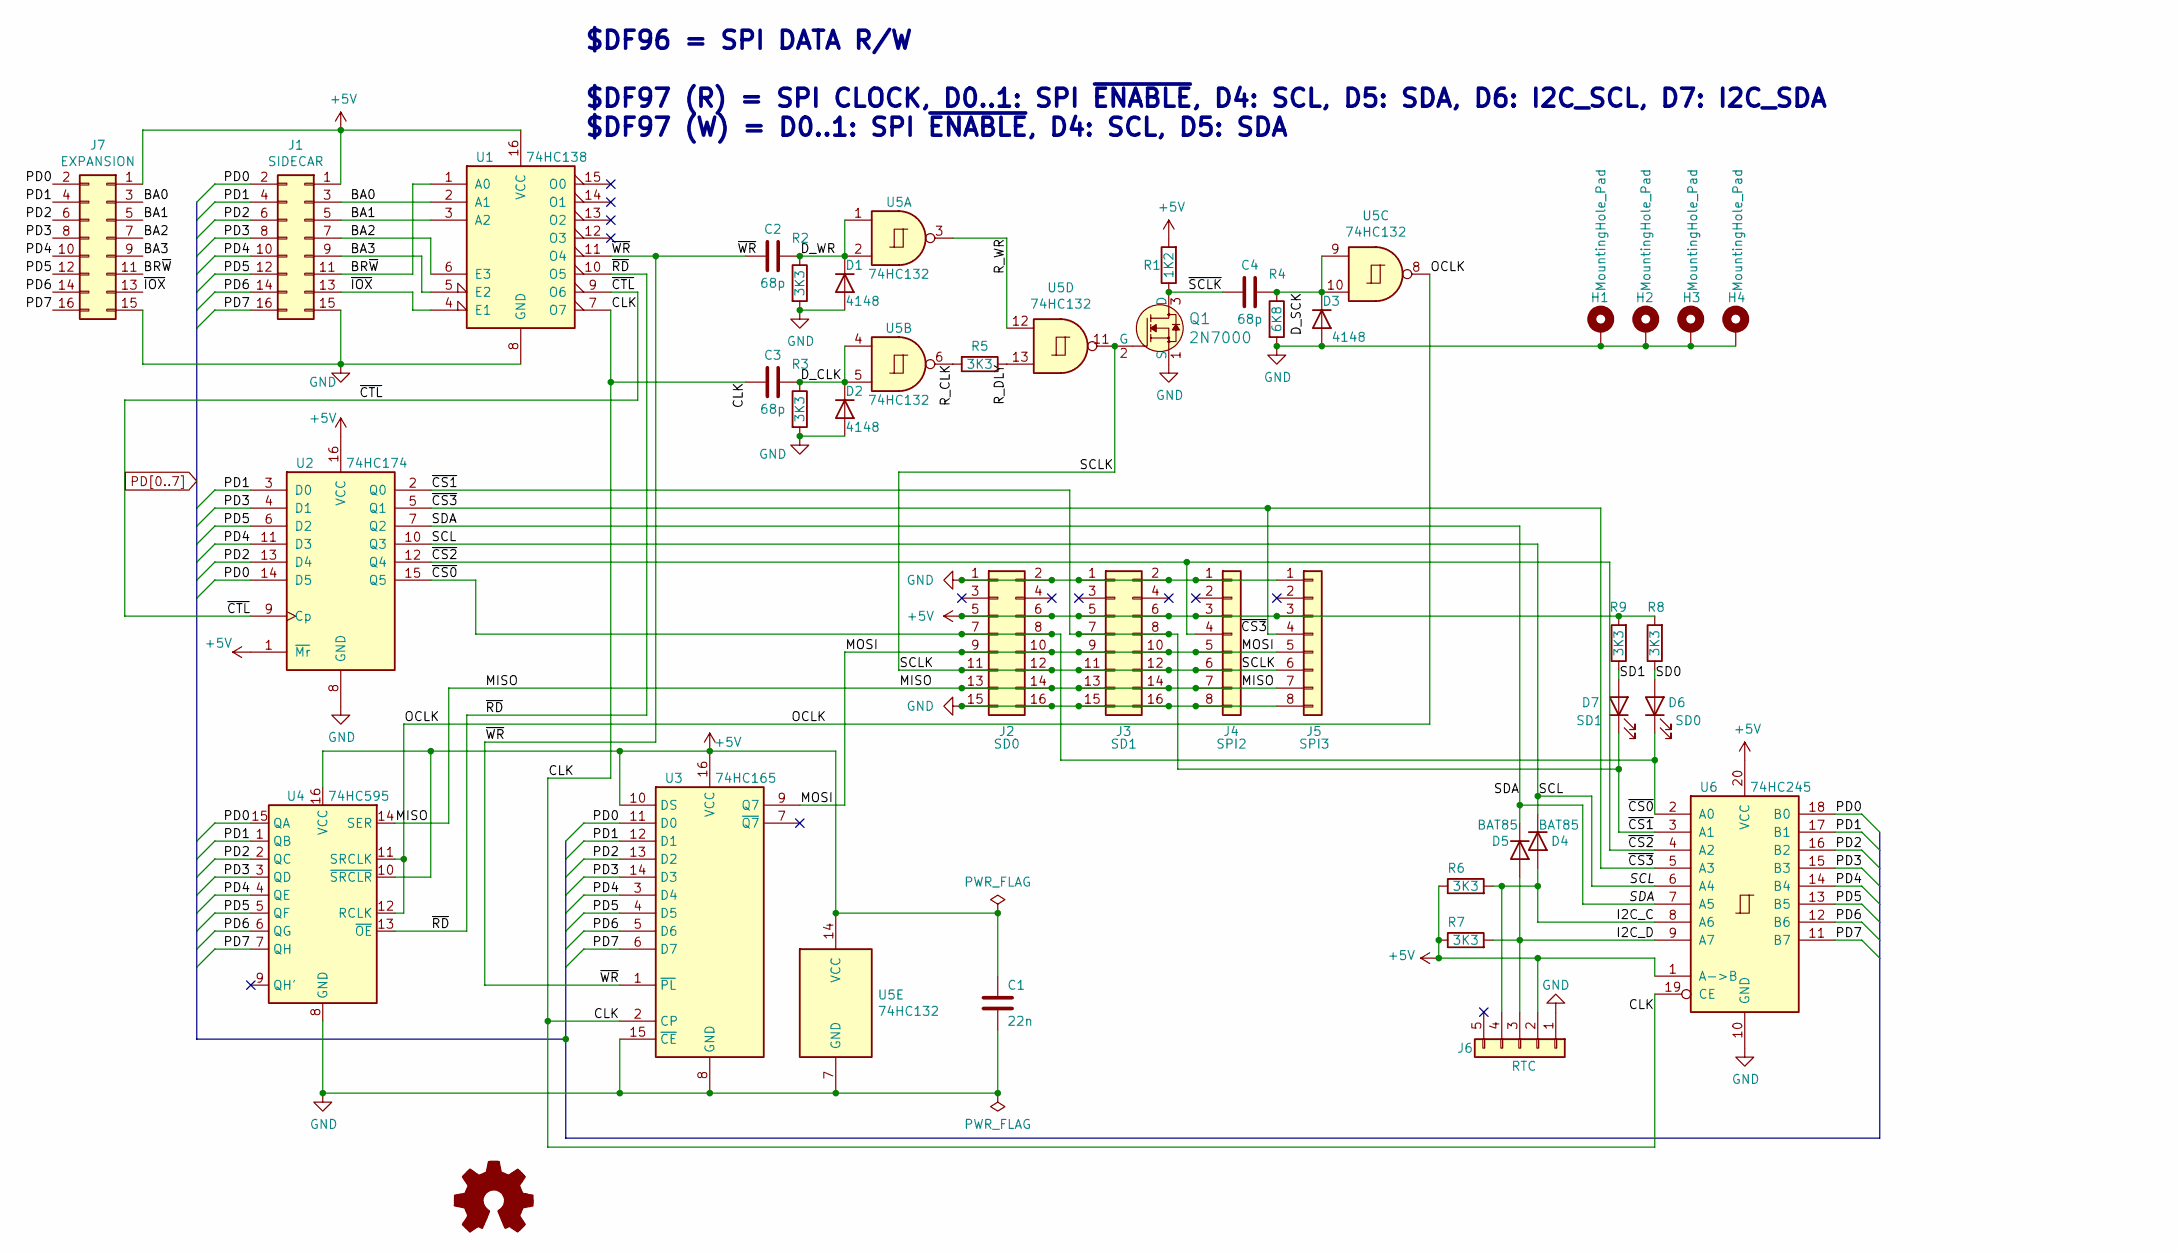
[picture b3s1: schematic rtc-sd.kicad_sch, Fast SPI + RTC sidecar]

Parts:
C1: 22n; C_Disc_D5.0mm_W2.5mm_P5.00mm
C2, C3, C4: 68p; C_Disc_D3.8mm_W2.6mm_P2.50mm
D1, D2, D3: 4148; D_DO-35_SOD27_P2.54mm_Vertical_AnodeUp
D4, D5: BAT85; D_DO-35_SOD27_P2.54mm_Vertical_AnodeUp
D6: SD0; LED_D3.0mm
D7: SD1; LED_D3.0mm
H1, H2, H3, H4: MountingHole_Pad; MountingHole_3.2mm_M3_DIN965_Pad
J1: SIDECAR; PinHeader_2x08_P2.54mm_Horizontal
J2: SD0; PinHeader_2x08_P2.54mm_Vertical
J3: SD1; PinHeader_2x08_P2.54mm_Vertical
J4: SPI2; PinHeader_1x08_P2.54mm_Vertical
J5: SPI3; PinHeader_1x08_P2.54mm_Vertical
J6: RTC; PinHeader_1x05_P2.54mm_Vertical
J7: EXPANSION; PinSocket_2x08_P2.54mm_Horizontal
LOGO1: Logo_Open_Hardware_Small; j300
Q1: 2N7000; TO-92_Inline; MPN 2N7000; Digi-Key_PN 2N7000FS-ND
R1: 1K2; R_Axial_DIN0207_L6.3mm_D2.5mm_P2.54mm_Vertical
R2, R3, R5, R6, R7, R8, R9: 3K3; R_Axial_DIN0207_L6.3mm_D2.5mm_P2.54mm_Vertical
R4: 6K8; R_Axial_DIN0207_L6.3mm_D2.5mm_P2.54mm_Vertical
U1: 74HC138; DIP-16_W7.62mm_Socket
U2: 74HC174; DIP-16_W7.62mm_Socket
U3: 74HC165; DIP-16_W7.62mm_Socket
U4: 74HC595; DIP-16_W7.62mm_Socket
U5: 74HC132; DIP-14_W7.62mm_Socket
U6: 74HC245; DIP-20_W7.62mm_Socket

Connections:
+5V: C1.1, J1.1, J2.5, J2.6, J3.5, J3.6, J4.3, J5.3, J6.2, J7.1, R1.2, R6.1, R7.1, R8.2, R9.2, U1.16 (VCC), U2.1 (~Mr), U2.16 (VCC), U3.10 (DS), U3.16 (VCC), U4.10 (~SRCLR), U4.16 (VCC), U5.14 (VCC), U6.1 (A->B), U6.20 (VCC)
/BA0: J1.3, J7.3, U1.2 (A1)
/BA1: J1.5, J7.5, U1.3 (A2)
/BA2: J1.7, J7.7, U1.6 (E3)
/BA3: J1.9, J7.9, U1.5 (E2)
/BR~W: J1.11, J7.11, U1.1 (A0)
/CLK: C3.2, U1.7 (O7), U3.2 (CP), U6.19 (CE)
/D_CLK: C3.1, D2.1 (K), R3.1, U5.4, U5.5
/D_SCK: C4.1, D3.1 (K), R4.1, U5.9, U5.10
/D_WR: C2.1, D1.1 (K), R2.1, U5.1, U5.2
/I2C_C: D4.2 (A), J6.4, R6.2, U6.8 (A6)
/I2C_D: D5.2 (A), J6.3, R7.2, U6.9 (A7)
/MISO: J2.13, J2.14, J3.13, J3.14, J4.7, J5.7, U4.14 (SER)
/MOSI: J2.9, J2.10, J3.9, J3.10, J4.5, J5.5, U3.9 (Q7)
/OCLK: U4.11 (SRCLK), U4.12 (RCLK), U5.8
/R_CLK: R5.2, U5.6
/R_DLY: R5.1, U5.13
/R_WR: U5.3, U5.12
/SCL: D4.1 (K), U2.10 (Q3), U6.6 (A4)
/SCLK: J2.11, J2.12, J3.11, J3.12, J4.6, J5.6, Q1.2 (G), U5.11
/SD0: D6.2 (A), R8.1
/SD1: D7.2 (A), R9.1
/SDA: D5.1 (K), U2.7 (Q2), U6.7 (A5)
/~CS0: D6.1 (K), J2.7, J2.8, U2.15 (Q5), U6.2 (A0)
/~CS1: D7.1 (K), J3.7, J3.8, U2.2 (Q0), U6.3 (A1)
/~CS2: J4.4, U2.12 (Q4), U6.4 (A2)
/~CS3: J5.4, U2.5 (Q1), U6.5 (A3)
/~CTL: U1.9 (O6), U2.9 (Cp)
/~IOX: J1.13, J7.13, U1.4 (E1)
/~RD: U1.10 (O5), U4.13 (~OE)
/~SCLK: C4.2, Q1.3 (D), R1.1
/~WR: C2.2, U1.11 (O4), U3.1 (~PL)
GND: C1.2, D1.2 (A), D2.2 (A), D3.2 (A), H1.1, H2.1, H3.1, H4.1, J1.15, J2.1, J2.2, J2.15, J2.16, J3.1, J3.2, J3.15, J3.16, J4.1, J4.8, J5.1, J5.8, J6.1, J7.15, Q1.1 (S), R2.2, R3.2, R4.2, U1.8 (GND), U2.8 (GND), U3.8 (GND), U3.15 (~CE), U4.8 (GND), U5.7 (GND), U6.10 (GND)
PD0: J1.2, J7.2, U2.14 (D5), U3.11 (D0), U4.15 (QA), U6.18 (B0)
PD1: J1.4, J7.4, U2.3 (D0), U3.12 (D1), U4.1 (QB), U6.17 (B1)
PD2: J1.6, J7.6, U2.13 (D4), U3.13 (D2), U4.2 (QC), U6.16 (B2)
PD3: J1.8, J7.8, U2.4 (D1), U3.14 (D3), U4.3 (QD), U6.15 (B3)
PD4: J1.10, J7.10, U2.11 (D3), U3.3 (D4), U4.4 (QE), U6.14 (B4)
PD5: J1.12, J7.12, U2.6 (D2), U3.4 (D5), U4.5 (QF), U6.13 (B5)
PD6: J1.14, J7.14, U3.5 (D6), U4.6 (QG), U6.12 (B6)
PD7: J1.16, J7.16, U3.6 (D7), U4.7 (QH), U6.11 (B7)

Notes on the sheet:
$DF96 = SPI DATA R/W $DF97 (R) = SPI CLOCK, D0..1: SPI ~{ENABLE}, D4: SCL, D5: SDA, D6: I2C_SCL, D7: I2C_SDA $DF97 (W) = D0..1: SPI ~{ENABLE}, D4: SCL, D5: SDA

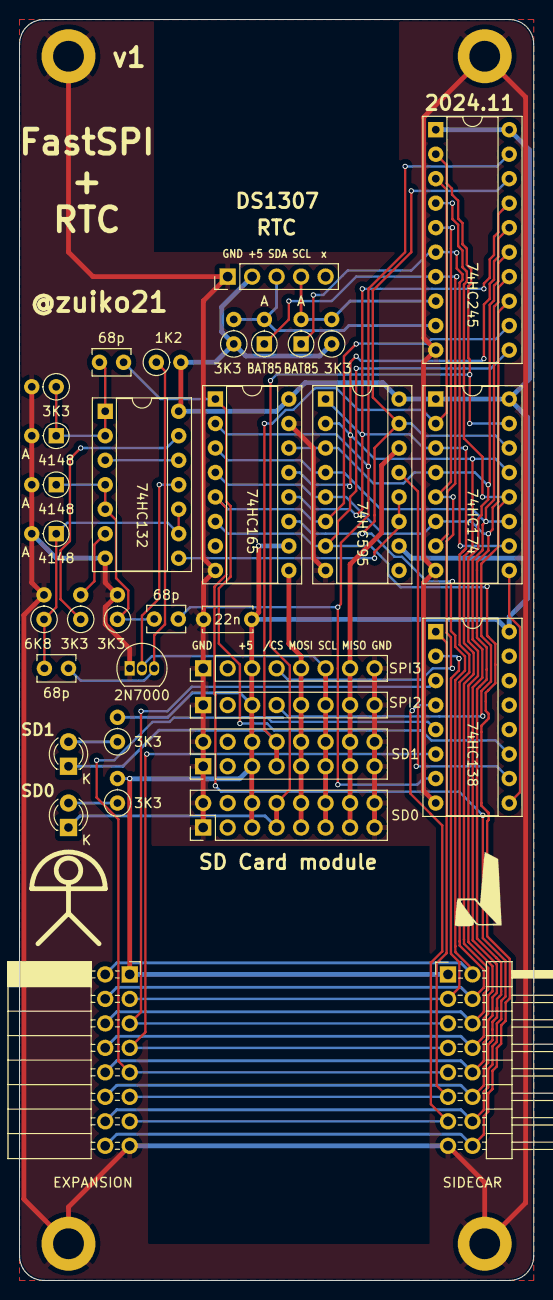
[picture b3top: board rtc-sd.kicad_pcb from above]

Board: 2 copper layers, 53.3 x 130.8 mm, 39 parts (0 on the bottom side), 41 nets.

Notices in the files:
hard/kicad/omronkbd/omronkbd.kicad_sch:
(c) 2023-2024 Carlos J. Santisteban
hard/kicad/rosario/rosario.sch:
(c) 2012-2024 Carlos J. Santisteban
